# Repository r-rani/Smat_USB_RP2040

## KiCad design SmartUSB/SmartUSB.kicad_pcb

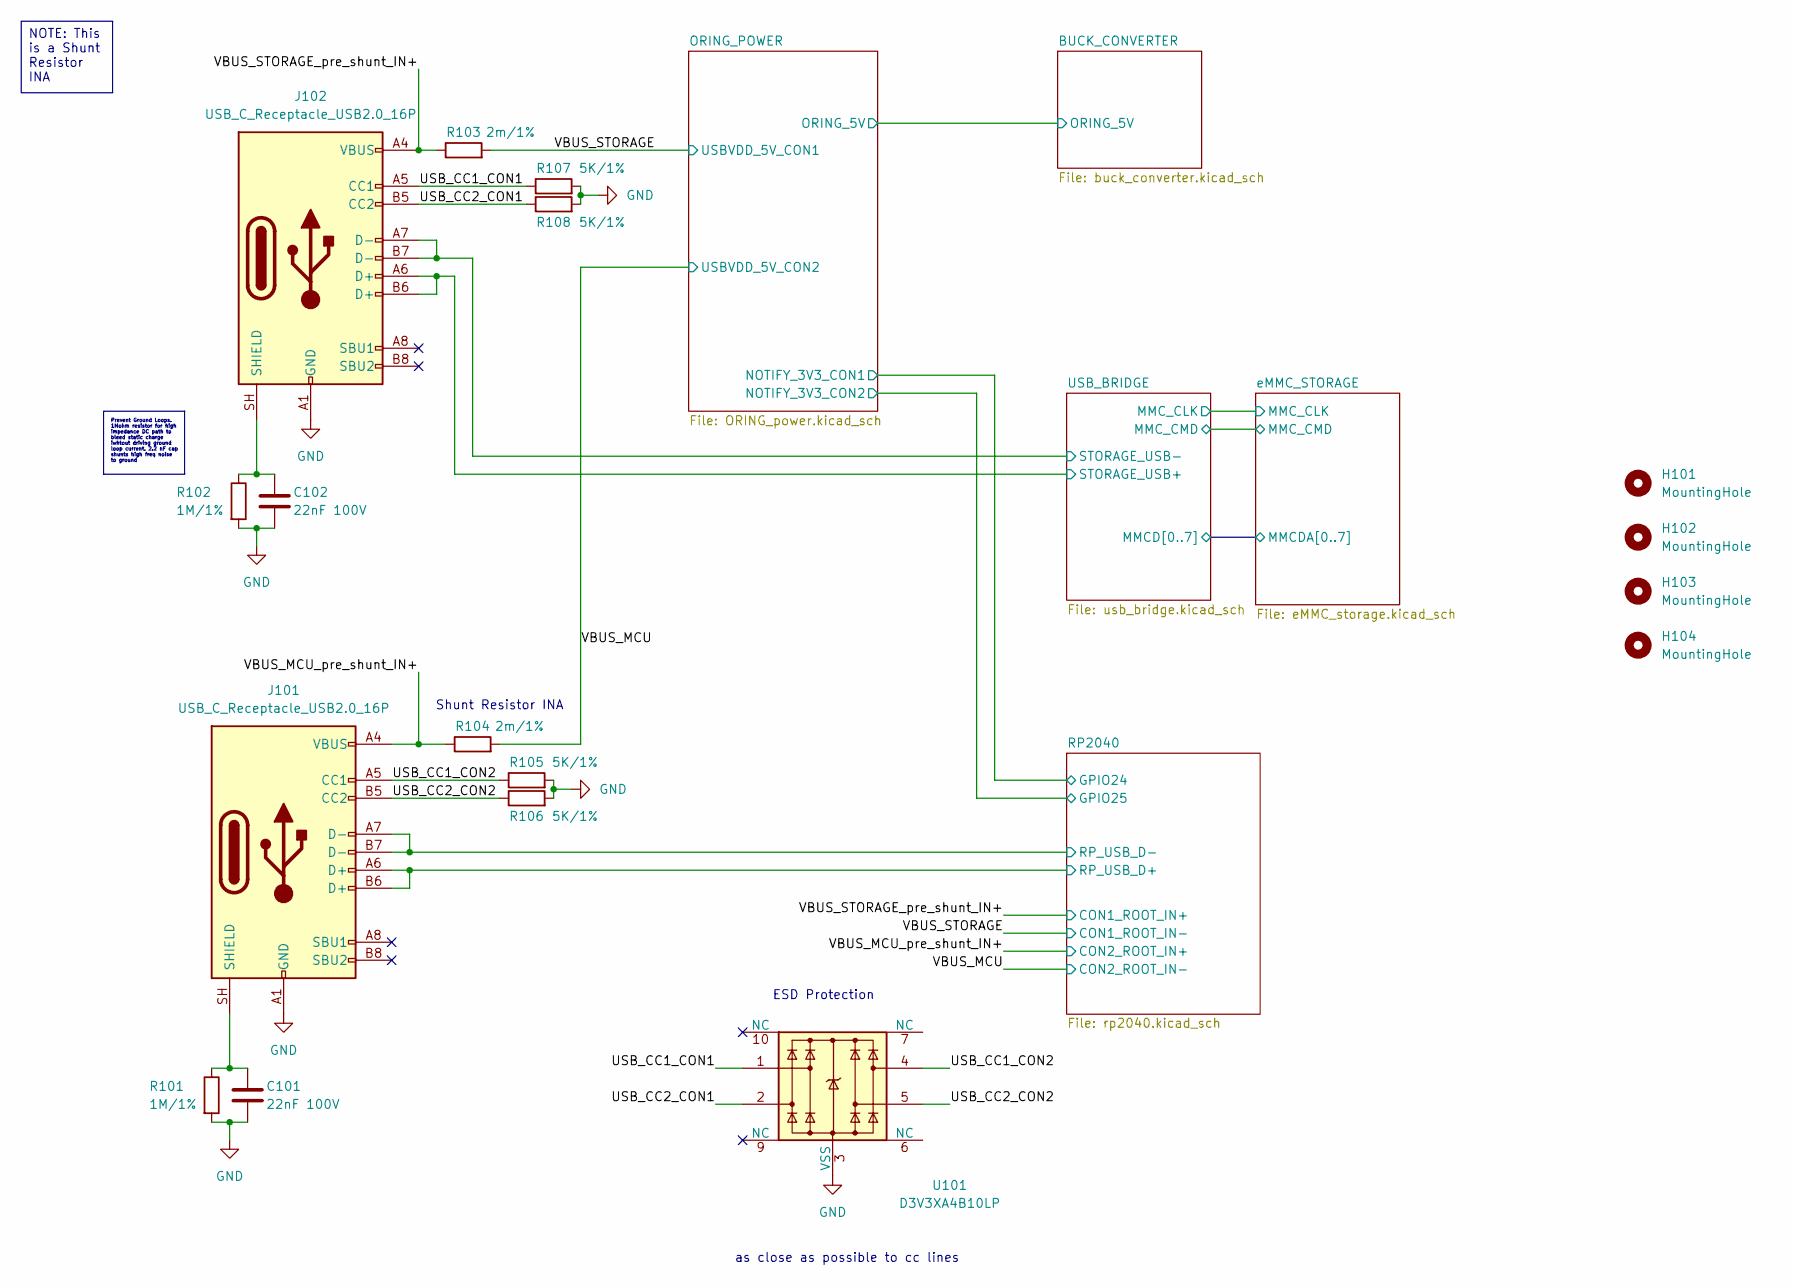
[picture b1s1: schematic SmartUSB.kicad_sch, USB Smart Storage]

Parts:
C101, C102: 22nF 100V; C_0603_1608Metric
H101, H102, H103, H104: MountingHole; Maple_Mini
J101, J102: USB_C_Receptacle_USB2.0_16P; USB_C_Receptacle_XKB_U262-16XN-4BVC11
R101, R102: 1M/1%; R_01005_0402Metric
R103, R104: 2m/1%; R_01005_0402Metric
R105, R106, R107, R108: 5K/1%; R_01005_0402Metric
U101: D3V3XA4B10LP; Diodes_UDFN-10_1x2.5mm_P0.5mm

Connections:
/RP2040/RP_USB_D+: J101.A6 (D+), J101.B6 (D+); also elsewhere on the board
/RP2040/RP_USB_D-: J101.A7 (D-), J101.B7 (D-); also elsewhere on the board
/USB_BRIDGE/STORAGE_USB+: J102.A6 (D+), J102.B6 (D+); also elsewhere on the board
/USB_BRIDGE/STORAGE_USB-: J102.A7 (D-), J102.B7 (D-); also elsewhere on the board
/USB_CC1_CON1: J102.A5 (CC1), R107.1, U101.1
/USB_CC1_CON2: J101.A5 (CC1), R105.1, U101.4
/USB_CC2_CON1: J102.B5 (CC2), R108.1, U101.2
/USB_CC2_CON2: J101.B5 (CC2), R106.1, U101.5
/VBUS_MCU: R104.2; also elsewhere on the board
/VBUS_MCU_pre_shunt_IN+: J101.A4 (VBUS), J101.A9 (VBUS), J101.B4 (VBUS), J101.B9 (VBUS), R104.1; also elsewhere on the board
/VBUS_STORAGE: R103.2; also elsewhere on the board
/VBUS_STORAGE_pre_shunt_IN+: J102.A4 (VBUS), J102.A9 (VBUS), J102.B4 (VBUS), J102.B9 (VBUS), R103.1; also elsewhere on the board
GND: C101.2, C102.2, J101.A1 (GND), J101.A12 (GND), J101.B1 (GND), J101.B12 (GND), J102.A1 (GND), J102.A12 (GND), J102.B1 (GND), J102.B12 (GND), R101.2, R102.2, R105.2, R106.2, R107.2, R108.2, U101.3 (VSS), U101.8 (VSS); also elsewhere on the board
unnamed: C101.1, J101.SH (SHIELD), R101.1
unnamed: C102.1, J102.SH (SHIELD), R102.1

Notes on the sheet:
Shunt Resistor INA
as close as possible to cc lines
ESD Protection
Prevent Ground Loops. 1Mohm resistor for high impedance DC path to bleed static charge iwhtout driving ground loop current. 2.2 nF cap shunts high freq noise to ground
NOTE: This is a Shunt Resistor INA

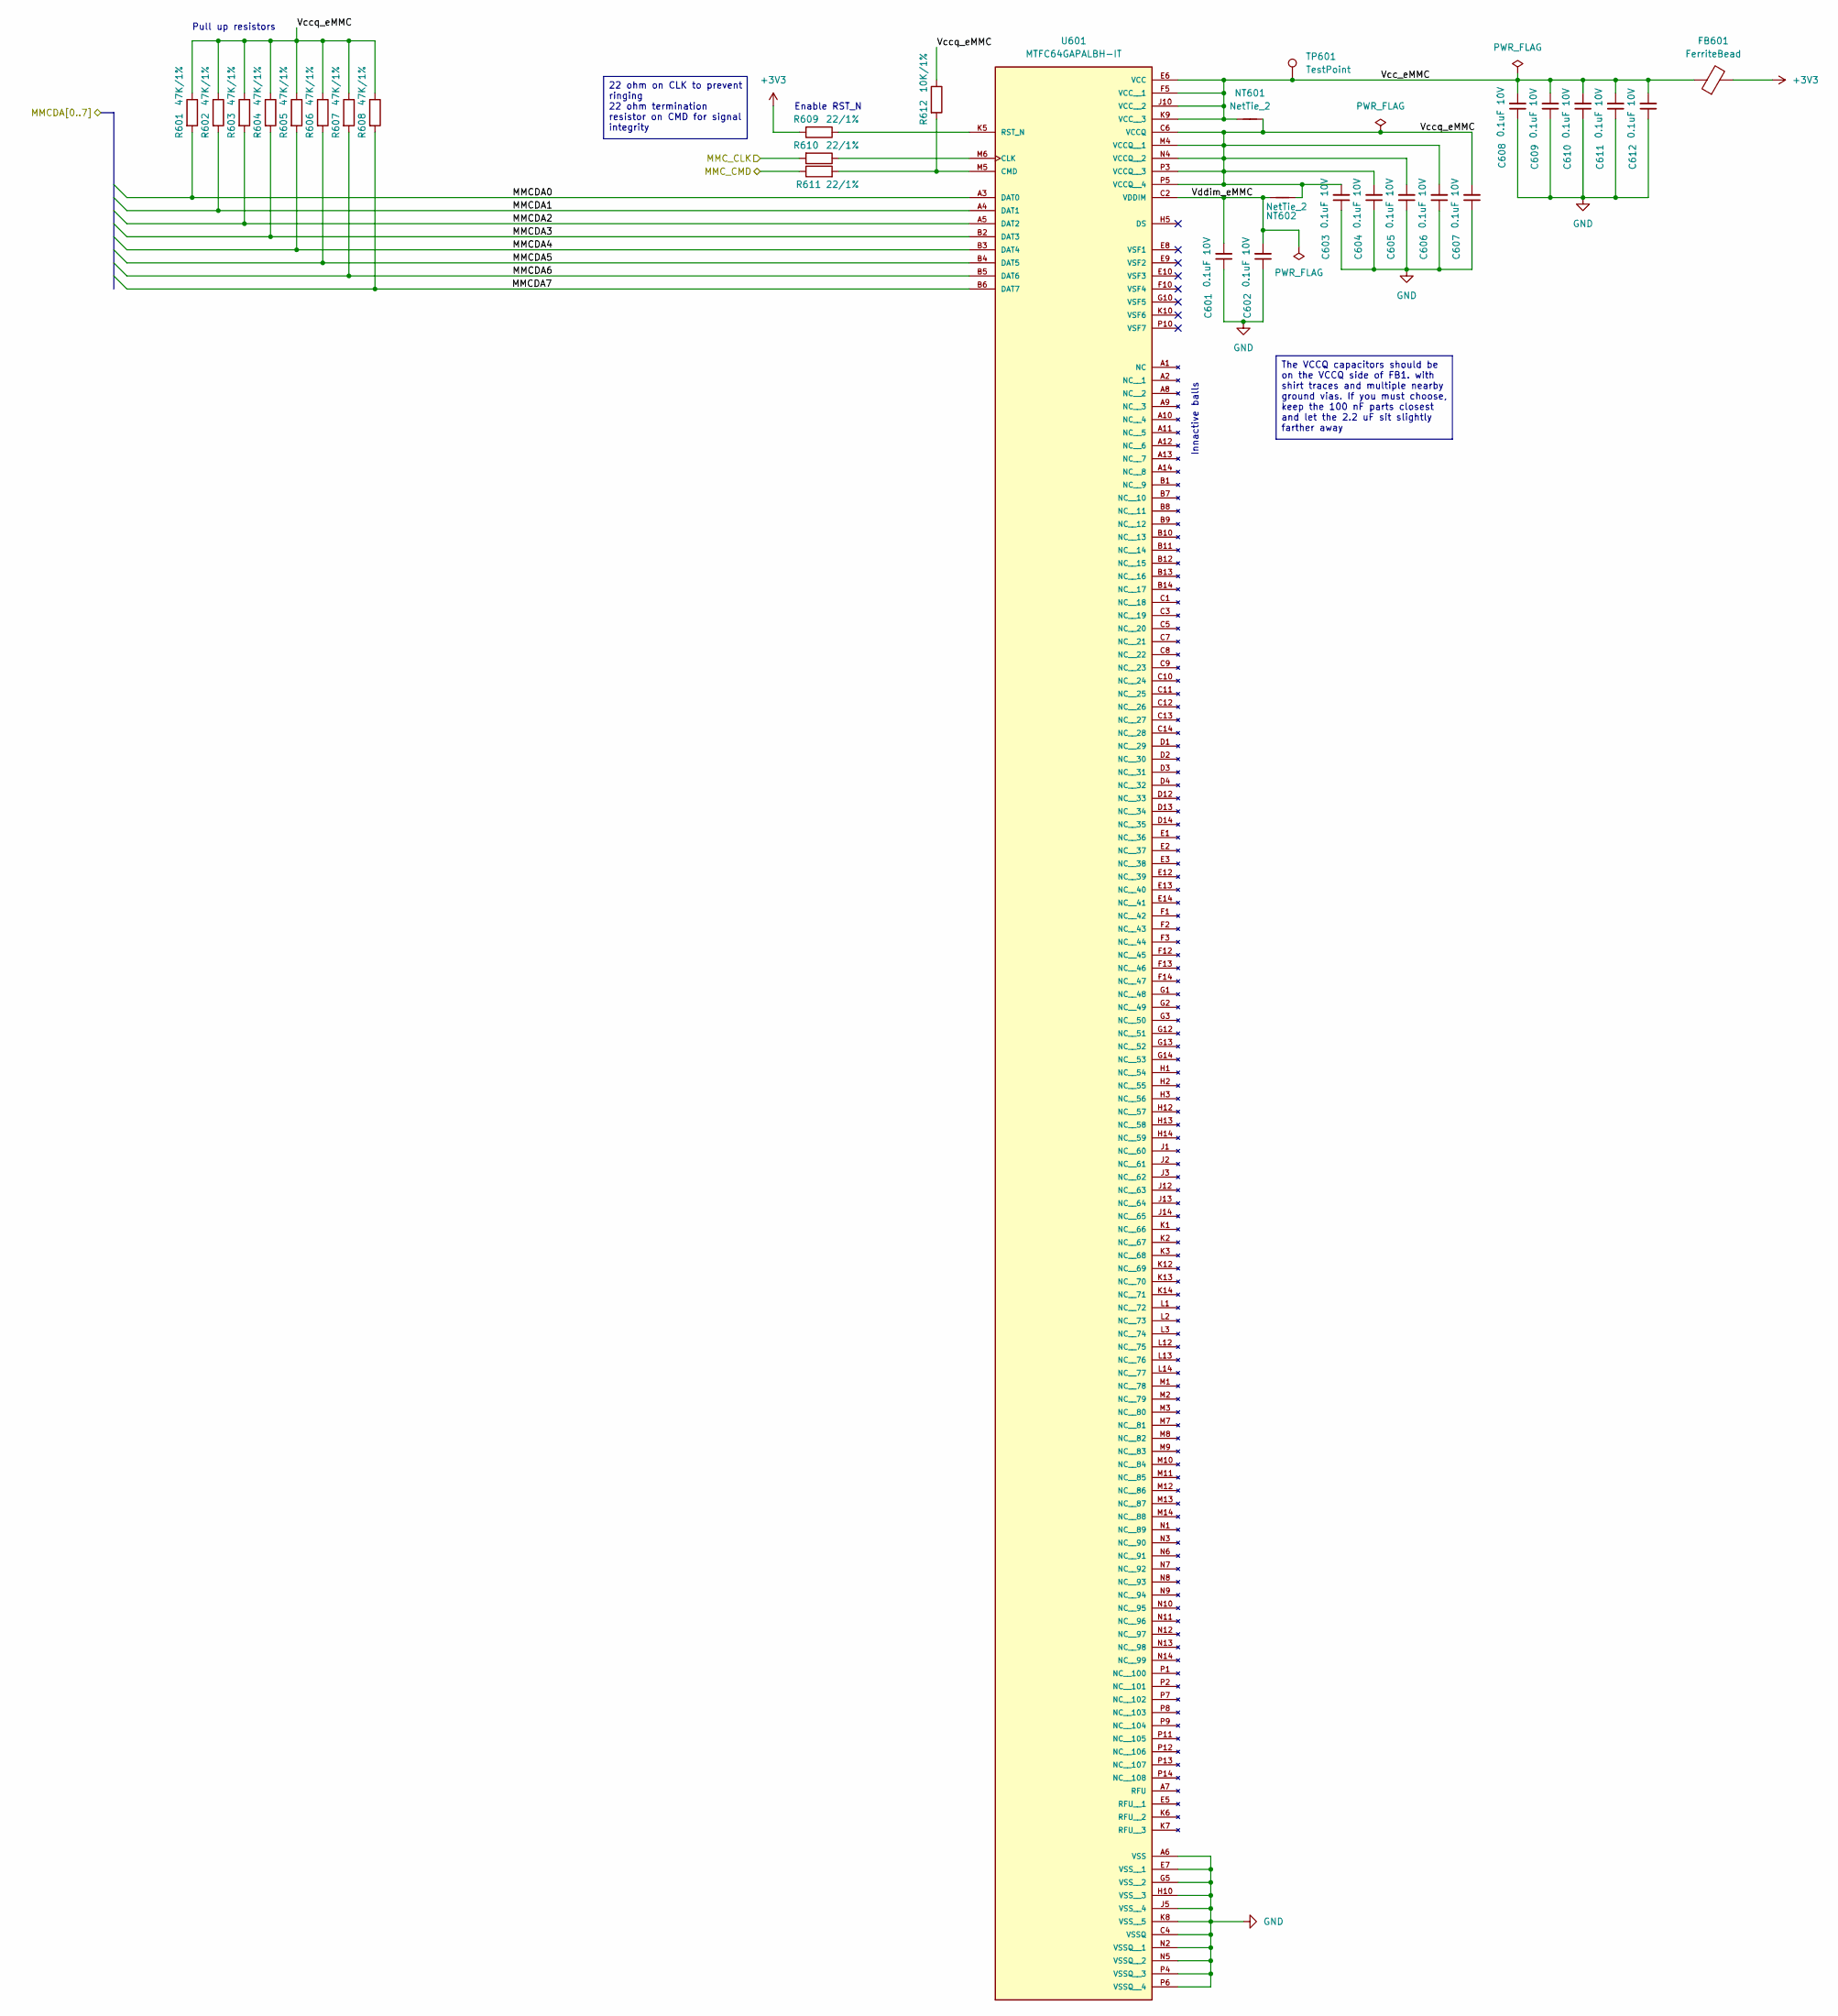
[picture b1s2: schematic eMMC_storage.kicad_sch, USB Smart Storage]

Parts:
C601, C602, C603, C604, C605, C606, C607, C608, C609, C610, C611, C612: 0.1uF 10V; C_0402_1005Metric
FB601: FerriteBead; L_Panasonic_PCC-M0530M
NT601, NT602: NetTie_2; NetTie-2_SMD_Pad0.5mm
R601, R602, R603, R604, R605, R606, R607, R608: 47K/1%; R_01005_0402Metric
R609, R610, R611: 22/1%; R_01005_0402Metric
R612: 10K/1%; R_01005_0402Metric
TP601: TestPoint; TestPoint_Pad_D1.5mm
U601: MTFC64GAPALBH-IT; BGA153N50P14X14_1300X1150X110N; PARTREV Rev. C 3/19 EN

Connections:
+3V3: FB601.2, R609.2; also elsewhere on the board
/USB_BRIDGE/MMCD0: R601.2, U601.A3 (DAT0); also elsewhere on the board
/USB_BRIDGE/MMCD1: R602.2, U601.A4 (DAT1); also elsewhere on the board
/USB_BRIDGE/MMCD2: R603.2, U601.A5 (DAT2); also elsewhere on the board
/USB_BRIDGE/MMCD3: R604.2, U601.B2 (DAT3); also elsewhere on the board
/USB_BRIDGE/MMCD4: R605.2, U601.B3 (DAT4); also elsewhere on the board
/USB_BRIDGE/MMCD5: R606.2, U601.B4 (DAT5); also elsewhere on the board
/USB_BRIDGE/MMCD6: R607.2, U601.B5 (DAT6); also elsewhere on the board
/USB_BRIDGE/MMCD7: R608.2, U601.B6 (DAT7); also elsewhere on the board
/USB_BRIDGE/MMC_CLK: R610.2; also elsewhere on the board
/USB_BRIDGE/MMC_CMD: R611.1; also elsewhere on the board
/eMMC_STORAGE/Vcc_eMMC: C608.2, C609.2, C610.2, C611.2, C612.2, FB601.1, NT601.1, TP601.1 (1_1), U601.E6 (VCC), U601.F5 (VCC__1), U601.J10 (VCC__2), U601.K9 (VCC__3)
/eMMC_STORAGE/Vccq_eMMC: C603.2, C604.2, C605.2, C606.2, C607.2, NT601.2, NT602.1, R601.1, R602.1, R603.1, R604.1, R605.1, R606.1, R607.1, R608.1, R612.1, U601.C6 (VCCQ), U601.M4 (VCCQ__1), U601.N4 (VCCQ__2), U601.P3 (VCCQ__3), U601.P5 (VCCQ__4)
/eMMC_STORAGE/Vddim_eMMC: C601.2, C602.2, NT602.2, U601.C2 (VDDIM)
GND: C601.1, C602.1, C603.1, C604.1, C605.1, C606.1, C607.1, C608.1, C609.1, C610.1, C611.1, C612.1, U601.A6 (VSS), U601.C4 (VSSQ), U601.E7 (VSS__1), U601.G5 (VSS__2), U601.H10 (VSS__3), U601.J5 (VSS__4), U601.K8 (VSS__5), U601.N2 (VSSQ__1), U601.N5 (VSSQ__2), U601.P4 (VSSQ__3), U601.P6 (VSSQ__4); also elsewhere on the board
unnamed: R610.1, U601.M6 (CLK)
unnamed: R611.2, R612.2, U601.M5 (CMD)
unnamed: R609.1, U601.K5 (RST_N)

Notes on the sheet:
Enable RST_N
Innactive balls
Pull up resistors
22 ohm on CLK to prevent ringing 22 ohm termination resistor on CMD for signal integrity
The VCCQ capacitors should be on the VCCQ side of FB1. with shirt traces and multiple nearby ground vias. If you must choose, keep the 100 nF parts closest and let the 2.2 uF sit slightly farther away

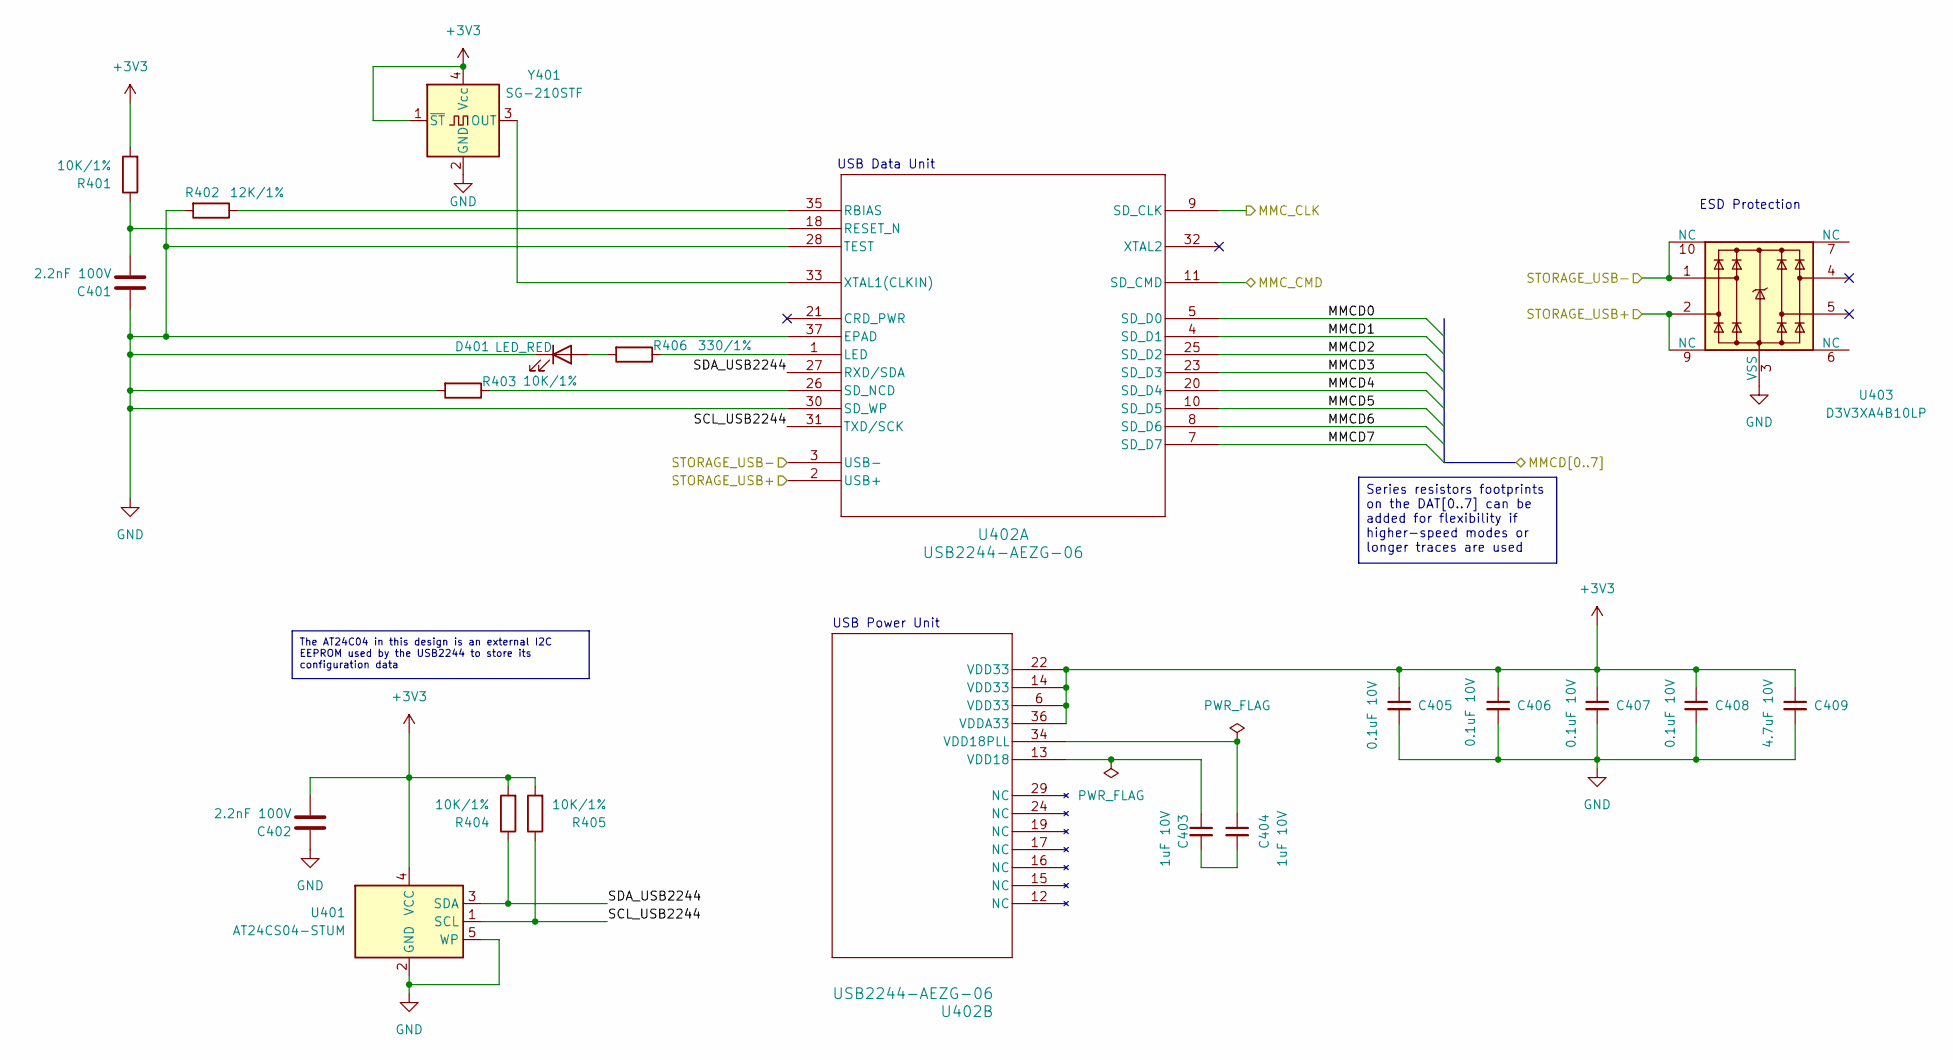
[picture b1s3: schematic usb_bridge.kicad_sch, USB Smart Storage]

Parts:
C401, C402: 2.2nF 100V; C_0603_1608Metric
C403, C404: 1uF 10V; C_0603_1608Metric
C405, C406, C407, C408: 0.1uF 10V; C_0603_1608Metric
C409: 4.7uF 10V; C_0603_1608Metric
D401: LED_RED; LED_0603_1608Metric
R401, R403, R404, R405: 10K/1%; R_01005_0402Metric
R402: 12K/1%; R_01005_0402Metric
R406: 330/1%; R_01005_0402Metric
U401: AT24CS04-STUM; SOT-23-5
U402: USB2244-AEZG-06; QFN36_6X6MC_MCH; digikey USB2244-AEZG-06-ND
U403: D3V3XA4B10LP; Diodes_UDFN-10_1x2.5mm_P0.5mm
Y401: SG-210STF; Oscillator_SMD_SeikoEpson_SG210-4Pin_2.5x2.0mm

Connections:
+3V3: C402.2, C405.1, C406.1, C407.1, C408.1, C409.1, R401.2, R404.2, R405.2, U401.4 (VCC), U402.6 (VDD33), U402.14 (VDD33), U402.22 (VDD33), U402.36 (VDDA33), Y401.1 (~ST), Y401.4 (Vcc); also elsewhere on the board
/USB_BRIDGE/MMCD0: U402.5 (SD_D0); also elsewhere on the board
/USB_BRIDGE/MMCD1: U402.4 (SD_D1); also elsewhere on the board
/USB_BRIDGE/MMCD2: U402.25 (SD_D2); also elsewhere on the board
/USB_BRIDGE/MMCD3: U402.23 (SD_D3); also elsewhere on the board
/USB_BRIDGE/MMCD4: U402.20 (SD_D4); also elsewhere on the board
/USB_BRIDGE/MMCD5: U402.10 (SD_D5); also elsewhere on the board
/USB_BRIDGE/MMCD6: U402.8 (SD_D6); also elsewhere on the board
/USB_BRIDGE/MMCD7: U402.7 (SD_D7); also elsewhere on the board
/USB_BRIDGE/MMC_CLK: U402.9 (SD_CLK); also elsewhere on the board
/USB_BRIDGE/MMC_CMD: U402.11 (SD_CMD); also elsewhere on the board
/USB_BRIDGE/SCL_USB2244: R405.1, U401.1 (SCL), U402.31 (TXD/SCK)
/USB_BRIDGE/SDA_USB2244: R404.1, U401.3 (SDA), U402.27 (RXD/SDA)
/USB_BRIDGE/STORAGE_USB+: U402.2 (USB+), U403.2, U403.9 (NC); also elsewhere on the board
/USB_BRIDGE/STORAGE_USB-: U402.3 (USB-), U403.1, U403.10 (NC); also elsewhere on the board
GND: C401.1, C402.1, C405.2, C406.2, C407.2, C408.2, C409.2, D401.1 (K), R402.2, R403.2, U401.2 (GND), U401.5 (WP), U402.28 (TEST), U402.30 (SD_WP), U402.37 (EPAD), U403.3 (VSS), U403.8 (VSS), Y401.2 (GND); also elsewhere on the board
unnamed: C403.2, C404.2
unnamed: D401.2 (A), R406.2
unnamed: R406.1, U402.1 (LED)
unnamed: R402.1, U402.35 (RBIAS)
unnamed: C401.2, R401.1, U402.18 (RESET_N)
unnamed: R403.1, U402.26 (SD_NCD)
unnamed: U402.33 (XTAL1(CLKIN)), Y401.3 (OUT)
unnamed: C403.1, U402.13 (VDD18)
unnamed: C404.1, U402.34 (VDD18PLL)

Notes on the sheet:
USB Power Unit
USB Data Unit
ESD Protection
The AT24C04 in this design is an external I2C EEPROM used by the USB2244 to store its configuration data
Series resistors footprints on the DAT[0..7] can be added for flexibility if higher-speed modes or longer traces are used

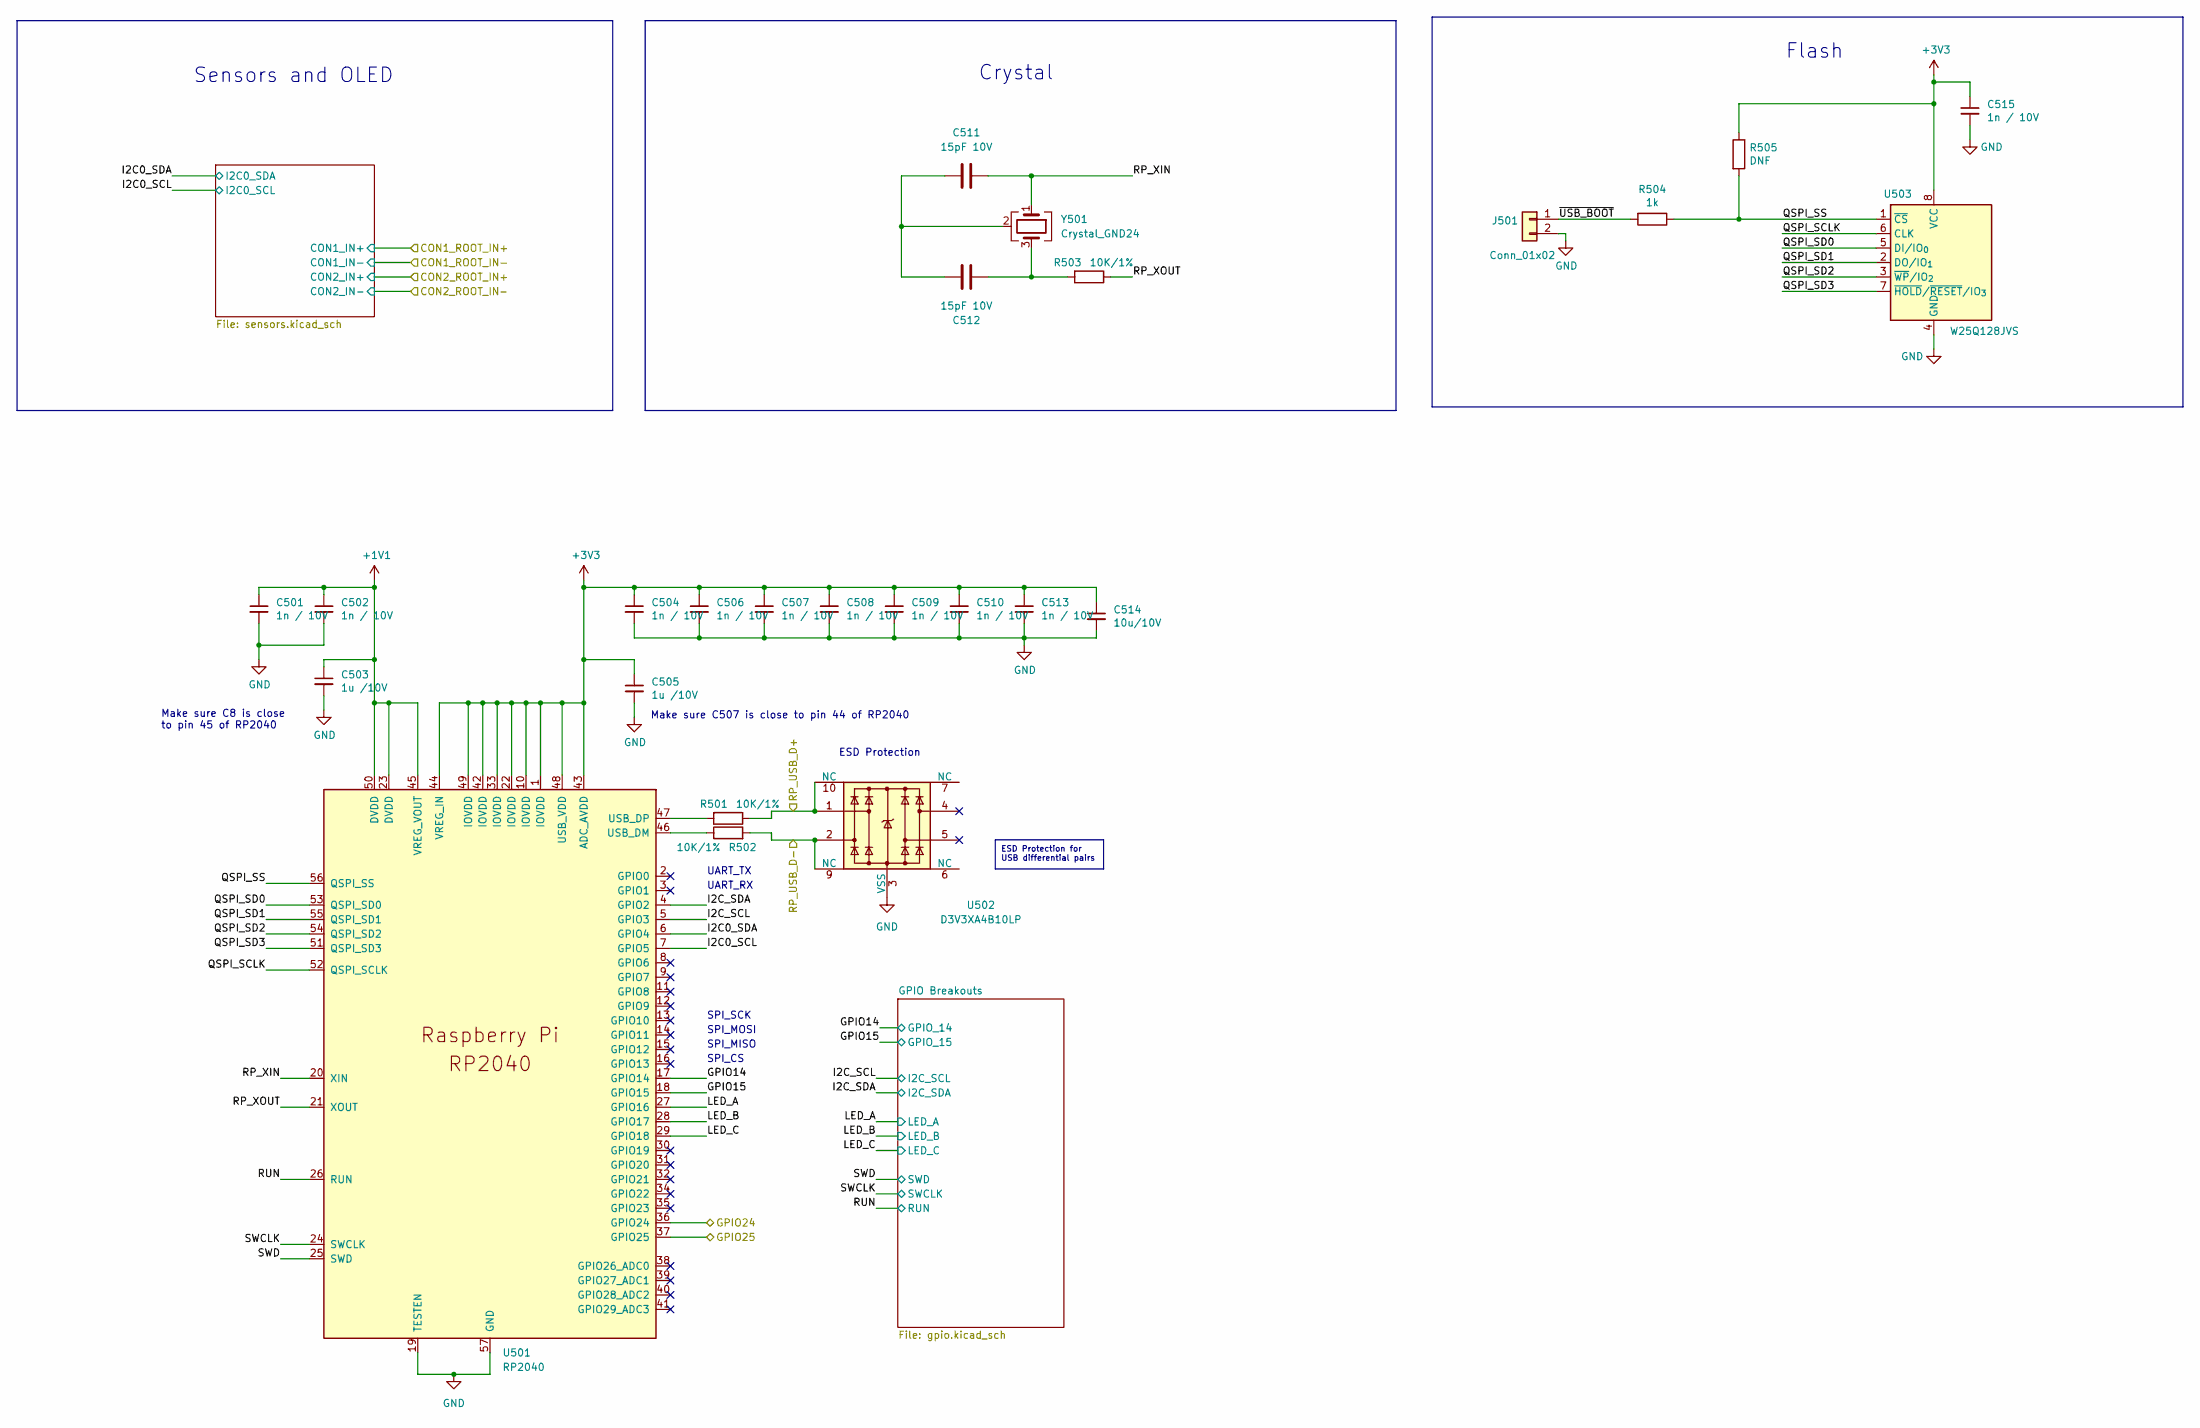
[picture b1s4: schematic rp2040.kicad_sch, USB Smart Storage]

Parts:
C501, C502, C504, C506, C507, C508, C509, C510, C513, C515: 1n / 10V; C_0603_1608Metric
C503, C505: 1u /10V; C_0603_1608Metric
C511, C512: 15pF 10V; C_0603_1608Metric
C514: 10u/10V; C_0805_2012Metric
J501: Conn_01x02; PinHeader_1x02_P2.54mm_Vertical
R501, R502, R503: 10K/1%; R_01005_0402Metric
R504: 1k; R_0402_1005Metric
R505: DNF; R_0402_1005Metric
U501: RP2040; RP2040-QFN-56
U502: D3V3XA4B10LP; Diodes_UDFN-10_1x2.5mm_P0.5mm
U503: W25Q128JVS; SOIC-8_5.3x5.3mm_P1.27mm
Y501: Crystal_GND24; Crystal_SMD_3225-4Pin_3.2x2.5mm

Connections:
+1V1: C501.1, C502.1, C503.1, U501.23 (DVDD), U501.45 (VREG_VOUT), U501.50 (DVDD)
+3V3: C504.1, C505.1, C506.1, C507.1, C508.1, C509.1, C510.1, C513.1, C514.1, C515.1, R505.1, U501.1 (IOVDD), U501.10 (IOVDD), U501.22 (IOVDD), U501.33 (IOVDD), U501.42 (IOVDD), U501.43 (ADC_AVDD), U501.44 (VREG_IN), U501.48 (USB_VDD), U501.49 (IOVDD), U503.8 (VCC); also elsewhere on the board
/ORING_POWER/NOTIFY_3V3_CON1: U501.36 (GPIO24); also elsewhere on the board
/ORING_POWER/NOTIFY_3V3_CON2: U501.37 (GPIO25); also elsewhere on the board
/RP2040/GPIO14: U501.17 (GPIO14); also elsewhere on the board
/RP2040/GPIO15: U501.18 (GPIO15); also elsewhere on the board
/RP2040/I2C0_SCL: U501.7 (GPIO5); also elsewhere on the board
/RP2040/I2C0_SDA: U501.6 (GPIO4); also elsewhere on the board
/RP2040/I2C_SCL: U501.5 (GPIO3); also elsewhere on the board
/RP2040/I2C_SDA: U501.4 (GPIO2); also elsewhere on the board
/RP2040/LED_A: U501.27 (GPIO16); also elsewhere on the board
/RP2040/LED_B: U501.28 (GPIO17); also elsewhere on the board
/RP2040/LED_C: U501.29 (GPIO18); also elsewhere on the board
/RP2040/QSPI_SCLK: U501.52 (QSPI_SCLK), U503.6 (CLK)
/RP2040/QSPI_SD0: U501.53 (QSPI_SD0), U503.5 (DI/IO_{0})
/RP2040/QSPI_SD1: U501.55 (QSPI_SD1), U503.2 (DO/IO_{1})
/RP2040/QSPI_SD2: U501.54 (QSPI_SD2), U503.3 (~WP/IO_{2})
/RP2040/QSPI_SD3: U501.51 (QSPI_SD3), U503.7 (~HOLD/~RESET/IO_{3})
/RP2040/QSPI_SS: R504.1, R505.2, U501.56 (QSPI_SS), U503.1 (~CS)
/RP2040/RP_USB_D+: R501.1, U502.1, U502.10 (NC); also elsewhere on the board
/RP2040/RP_USB_D-: R502.2, U502.2, U502.9 (NC); also elsewhere on the board
/RP2040/RP_XIN: C511.2, U501.20 (XIN), Y501.1
/RP2040/RP_XOUT: R503.1, U501.21 (XOUT)
/RP2040/RUN: U501.26 (RUN); also elsewhere on the board
/RP2040/SWCLK: U501.24 (SWCLK); also elsewhere on the board
/RP2040/SWD: U501.25 (SWD); also elsewhere on the board
/RP2040/~USB_BOOT: J501.1, R504.2
GND: C501.2, C502.2, C503.2, C504.2, C505.2, C506.2, C507.2, C508.2, C509.2, C510.2, C513.2, C514.2, C515.2, J501.2, U501.19 (TESTEN), U501.57 (GND), U502.3 (VSS), U502.8 (VSS), U503.4 (GND); also elsewhere on the board
unnamed: C511.1, C512.2, Y501.2 (G), Y501.4 (G)
unnamed: C512.1, R503.2, Y501.3
unnamed: R502.1, U501.46 (USB_DM)
unnamed: R501.2, U501.47 (USB_DP)

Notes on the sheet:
SPI_SCK
SPI_MISO
Make sure C507 is close to pin 44 of RP2040
ESD Protection
Make sure C8 is close to pin 45 of RP2040
Crystal
SPI_CS
UART_RX
SPI_MOSI
Flash
Sensors and OLED
UART_TX
ESD Protection for USB differential pairs

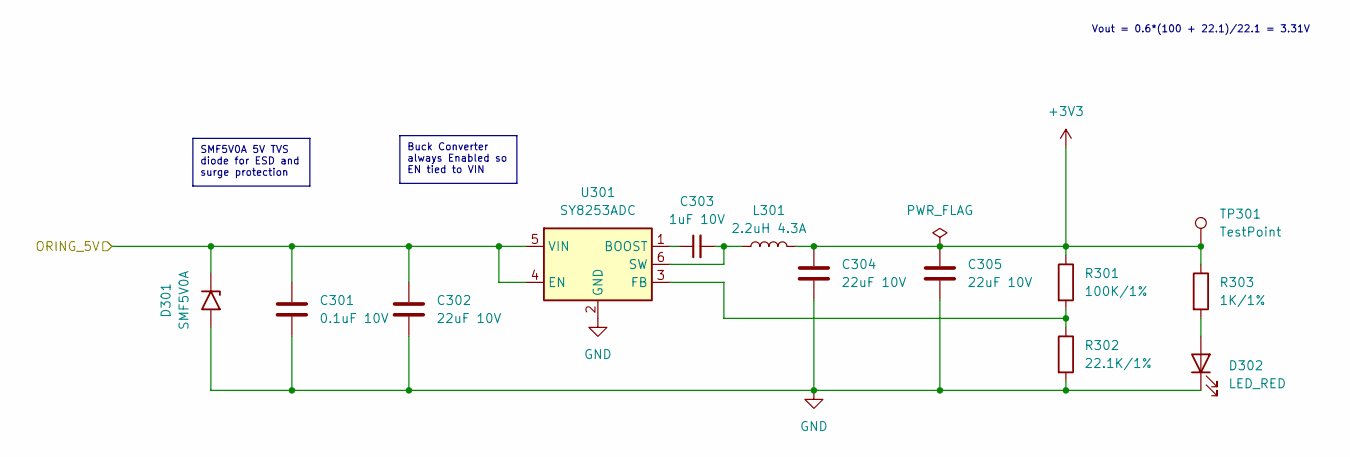
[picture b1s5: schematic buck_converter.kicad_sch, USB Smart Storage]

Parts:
C301: 0.1uF 10V; C_0603_1608Metric
C302, C304, C305: 22uF 10V; C_0805_2012Metric
C303: 1uF 10V; C_0603_1608Metric
D301: SMF5V0A; D_SMF
D302: LED_RED; LED_0603_1608Metric
L301: 2.2uH 4.3A; L_Sunlord_SWPA4020S
R301: 100K/1%; R_01005_0402Metric
R302: 22.1K/1%; R_01005_0402Metric
R303: 1K/1%; R_01005_0402Metric
TP301: TestPoint; TestPoint_Pad_D1.5mm
U301: SY8253ADC; TSOT-23-6

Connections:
+3V3: C304.1, C305.1, L301.2, R301.1, R303.1, TP301.1 (1_1); also elsewhere on the board
/BUCK_CONVERTER/ORING_5V: C301.1, C302.1, D301.1 (A1), U301.4 (EN), U301.5 (VIN); also elsewhere on the board
GND: C301.2, C302.2, C304.2, C305.2, D301.2 (A2), D302.1 (K), R302.2, U301.2 (GND); also elsewhere on the board
unnamed: D302.2 (A), R303.2
unnamed: C303.1, U301.1 (BOOST)
unnamed: R301.2, R302.1, U301.3 (FB)
unnamed: C303.2, L301.1, U301.6 (SW)

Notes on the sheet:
Vout = 0.6*(100 + 22.1)/22.1 = 3.31V
SMF5V0A 5V TVS diode for ESD and surge protection
Buck Converter always Enabled so EN tied to VIN

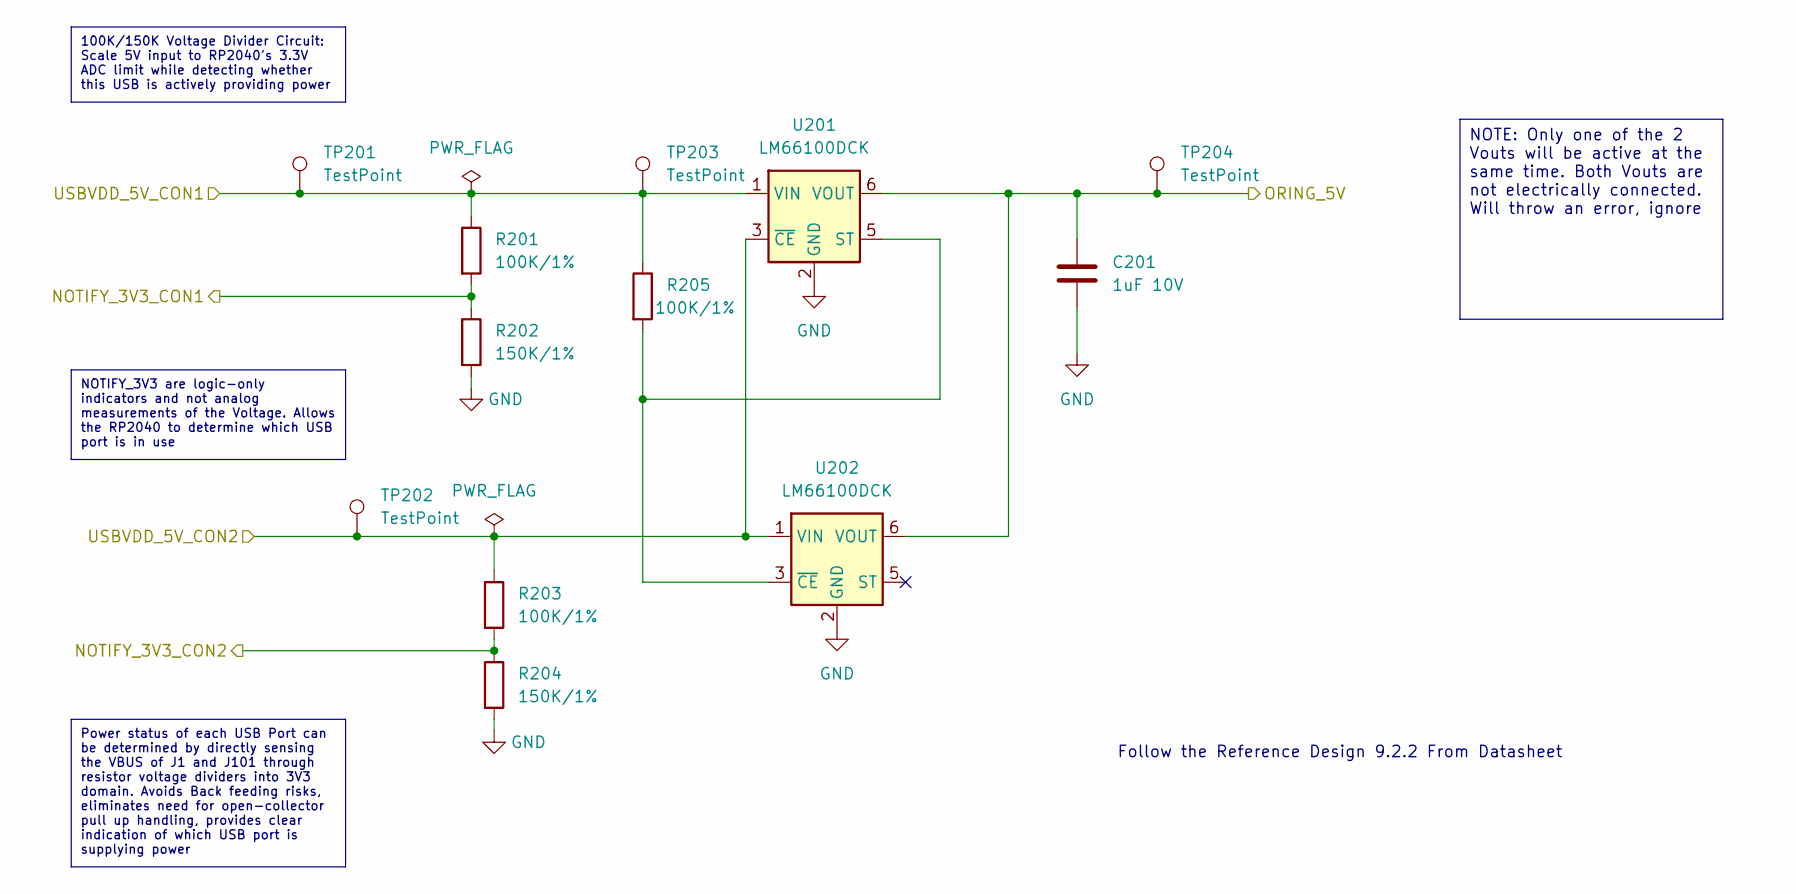
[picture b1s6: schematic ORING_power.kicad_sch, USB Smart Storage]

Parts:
C201: 1uF 10V; C_0603_1608Metric
R201, R203, R205: 100K/1%; R_01005_0402Metric
R202, R204: 150K/1%; R_01005_0402Metric
TP201, TP202, TP203, TP204: TestPoint; TestPoint_Pad_D1.5mm
U201, U202: LM66100DCK; SOT-363_SC-70-6

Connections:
/BUCK_CONVERTER/ORING_5V: C201.1, TP204.1 (1_1), U201.6 (VOUT), U202.6 (VOUT); also elsewhere on the board
/ORING_POWER/NOTIFY_3V3_CON1: R201.2, R202.1; also elsewhere on the board
/ORING_POWER/NOTIFY_3V3_CON2: R203.2, R204.1; also elsewhere on the board
/VBUS_MCU: R203.1, TP202.1 (1_1), U201.3 (~CE), U202.1 (VIN); also elsewhere on the board
/VBUS_STORAGE: R201.1, R205.1, TP201.1 (1_1), TP203.1 (1_1), U201.1 (VIN); also elsewhere on the board
GND: C201.2, R202.2, R204.2, U201.2 (GND), U202.2 (GND); also elsewhere on the board
unnamed: R205.2, U201.5 (ST), U202.3 (~CE)

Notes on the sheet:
Follow the Reference Design 9.2.2 From Datasheet
100K/150K Voltage Divider Circuit: Scale 5V input to RP2040's 3.3V ADC limit while detecting whether this USB is actively providing power
NOTIFY_3V3 are logic-only indicators and not analog measurements of the Voltage. Allows the RP2040 to determine which USB port is in use
Power status of each USB Port can be determined by directly sensing the VBUS of J1 and J101 through resistor voltage dividers into 3V3 domain. Avoids Back feeding risks, eliminates need for open-collector pull up handling, provides clear indication of which USB port is supplying power
NOTE: Only one of the 2 Vouts will be active at the same time. Both Vouts are not electrically connected. Will throw an error, ignore

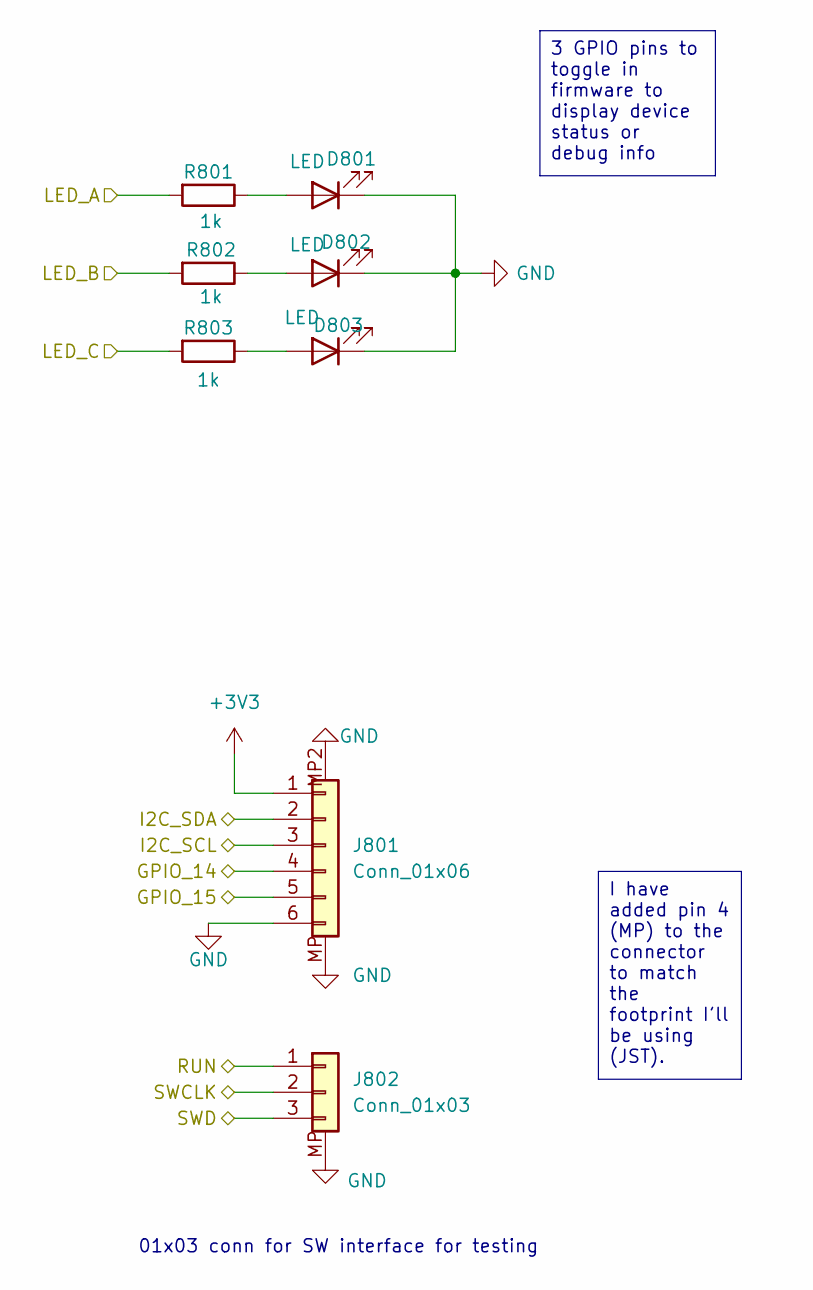
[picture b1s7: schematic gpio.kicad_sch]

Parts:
D801, D802, D803: LED; LED_0603_1608Metric
J801: Conn_01x06; JST_SHL_SM06B-SHLS-TF_1x06-1MP_P1.00mm_Horizontal
J802: Conn_01x03; JST_GH_SM03B-GHS-TB_1x03-1MP_P1.25mm_Horizontal
R801, R802, R803: 1k; R_0402_1005Metric

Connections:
+3V3: J801.1; also elsewhere on the board
/RP2040/GPIO14: J801.4; also elsewhere on the board
/RP2040/GPIO15: J801.5; also elsewhere on the board
/RP2040/I2C_SCL: J801.3; also elsewhere on the board
/RP2040/I2C_SDA: J801.2; also elsewhere on the board
/RP2040/LED_A: R801.2; also elsewhere on the board
/RP2040/LED_B: R802.2; also elsewhere on the board
/RP2040/LED_C: R803.2; also elsewhere on the board
/RP2040/RUN: J802.1; also elsewhere on the board
/RP2040/SWCLK: J802.2; also elsewhere on the board
/RP2040/SWD: J802.3; also elsewhere on the board
GND: D801.1 (K), D802.1 (K), D803.1 (K), J801.6, J801.MP, J801.MP2, J802.MP; also elsewhere on the board
unnamed: D801.2 (A), R801.1
unnamed: D802.2 (A), R802.1
unnamed: D803.2 (A), R803.1

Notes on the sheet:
01x03 conn for SW interface for testing
3 GPIO pins to toggle in firmware to display device status or debug info
I have added pin 4 (MP) to the connector to match the footprint I'll be using (JST).
